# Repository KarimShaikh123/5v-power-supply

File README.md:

# 5v-power-supply
12 V to 5 V regulated power supply designed in LTspice and KiCad, including schematic, PCB layout, simulation, and documentation.

## Overview

A linear regulated power supply designed to convert a 12 V DC input into a 5 V DC output. The project uses LTspice for circuit simulation and KiCad for schematic capture and PCB layout.

## Project Goals

* Design a regulated 5 V power supply.
* Simulate circuit behaviour in LTspice.
* Create a schematic and PCB layout in KiCad.
* Document the design process and engineering decisions.

## Design

* **Input:** 12 V DC
* **Output:** 5 V DC nominal
* **Regulator:** LT1086-5.0
* **Output capacitor:** 10 µF
* **Power indicator:** LED with a 1 kΩ series resistor
* **Connections:** 2-pin input and output connectors

## Tools

* LTspice — circuit simulation
* KiCad — schematic capture and PCB design
* GitHub — version control and documentation

## Repository Structure

* `schematic/` — KiCad schematic
* `pcb/` — KiCad PCB layout
* `simulation/` — LTspice simulation file
* `images/` — PCB renders and screenshots

## Validation

The initial LTspice simulation produced approximately 5.003 V at the output under a 1 kΩ load. The PCB layout passed KiCad's design-rule check.

**Note:** Simulation results and PCB design-rule checks do not replace physical testing. Output regulation, thermal performance, and correct operation should be verified before connecting real hardware.

## Future Improvements

* Verify the final circuit against the regulator datasheet.
* Perform further simulation and load testing.
* Fabricate and test the PCB.
* Document measured results and design revisions.

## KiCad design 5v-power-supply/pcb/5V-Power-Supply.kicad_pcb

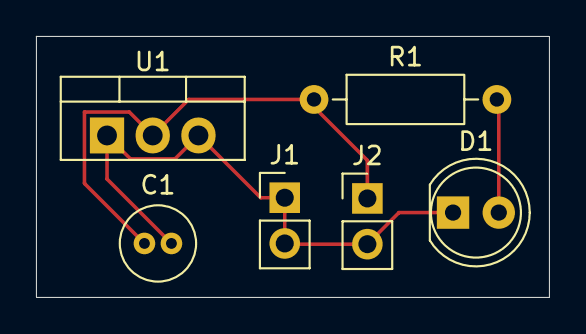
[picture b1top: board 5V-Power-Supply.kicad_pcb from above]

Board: 2 copper layers, 28.5 x 14.5 mm, 6 parts (0 on the bottom side), 3 nets.

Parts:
C1: 10; C_Radial_D4.0mm_H5.0mm_P1.50mm
D1: LED; LED_D5.0mm
J1, J2: Conn_01x02; PinHeader_1x02_P2.54mm_Vertical
R1: 1k; R_Axial_DIN0207_L6.3mm_D2.5mm_P10.16mm_Horizontal
U1: LT1086-5.0; TO-220-3_Vertical

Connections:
GND: C1.2, D1.1 (K), J1.1, J1.2, J2.2, U1.1 (GND), U1.3 (VI)
unnamed: D1.2 (A), R1.2
unnamed: C1.1, J2.1, R1.1, U1.2 (VO)
